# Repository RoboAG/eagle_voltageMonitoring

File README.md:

# eagle_voltageMonitoring
Simple voltage monitoring circuit

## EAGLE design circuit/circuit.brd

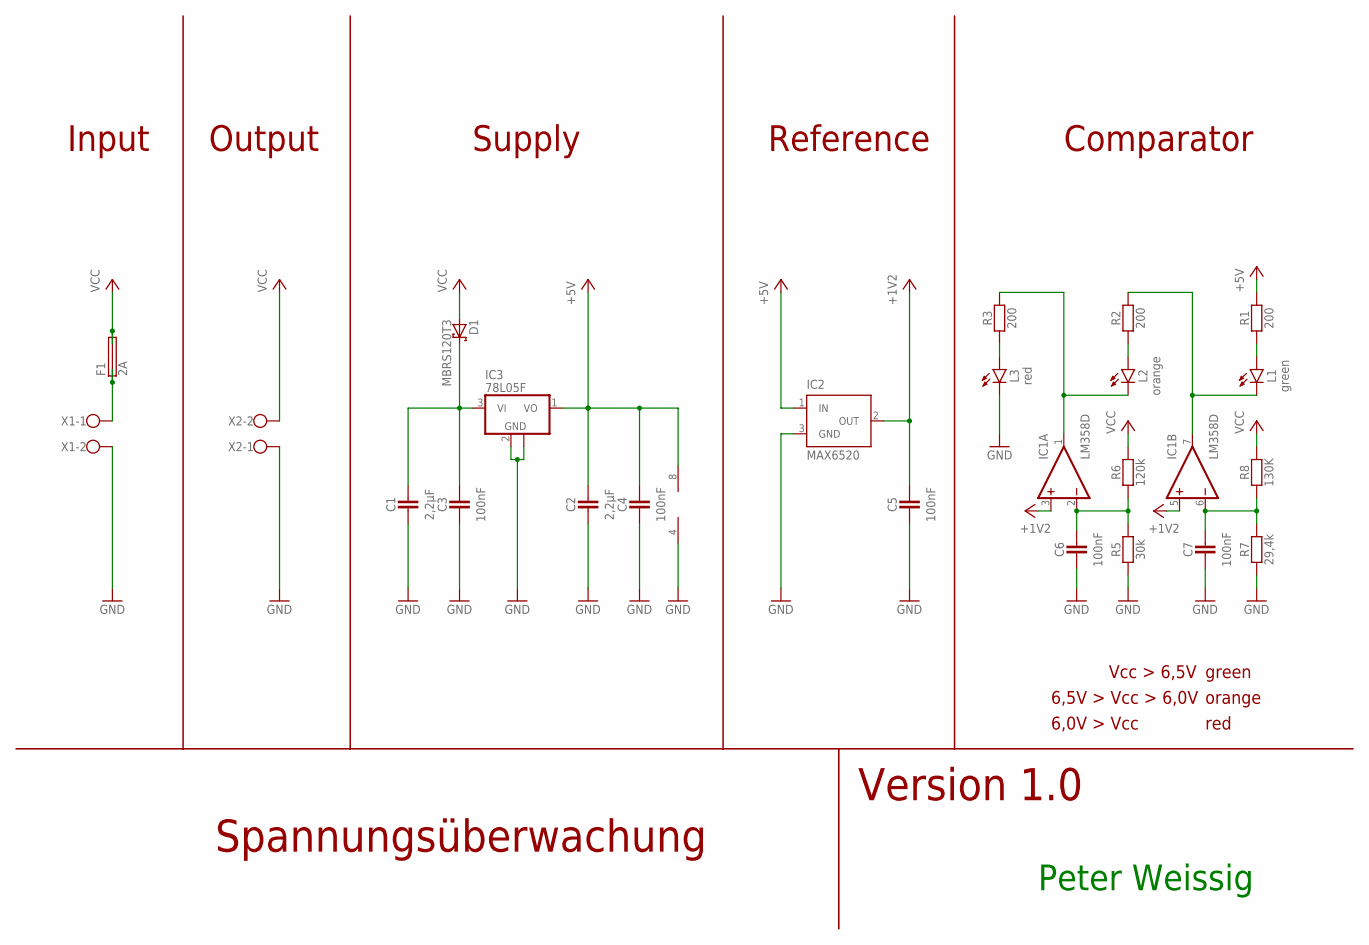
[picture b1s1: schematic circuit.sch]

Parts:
C1, C2: 2,2µF; SMD_1206
C3, C4, C5, C6, C7: 100nF; SMD_1206
D1: MBRS120T3; SMB
F1: 2A; SHK20L
IC1: LM358D; SO08
IC2: MAX6520; SOT23
IC3: 78L05F; SOT89
L1: green; LED_3MM
L2: orange; LED_3MM
L3: red; LED_3MM
R1, R2, R3: 200; SMD_1206
R5: 30k; SMD_1206
R6: 120k; SMD_1206
R7: 29,4k; SMD_1206
R8: 130K; SMD_1206
X1, X2: W237-102

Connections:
+3V3: C5.1, IC1.3 (+IN), IC1.5 (+IN), IC2.2 (OUT)
+5V: C2.1, C4.1, IC1.8 (V+), IC2.1 (IN), IC3.1 (VO), R1.1
GND: C1.2, C2.2, C3.2, C4.2, C5.2, C6.2, C7.2, IC1.4 (V-), IC2.3 (GND), IC3.2 (GND), IC3.2@1 (GND), L3.K (C), R5.1, R7.1, X1.2, X2.1
unnamed: C6.1, IC1.2 (-IN), R5.2, R6.1
unnamed: F1.1A, F1.1B, X1.1
unnamed: C7.1, IC1.6 (-IN), R7.2, R8.1
unnamed: C1.1, C3.1, D1.C, IC3.3 (VI)
unnamed: L1.A, R1.2
unnamed: IC1.7 (OUT), L1.K (C), R2.1
unnamed: L3.A, R3.2
unnamed: IC1.1 (OUT), L2.K (C), R3.1
unnamed: L2.A, R2.2
VCC: D1.A, F1.2A, F1.2B, R6.2, R8.2, X2.2

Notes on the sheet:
Input
Spannungsüberwachung
Peter Weissig
Version 1.0
Supply
Comparator
Output
Reference
Vcc > 6,5V
6,5V > Vcc > 6,0V
6,0V > Vcc
green
orange
red

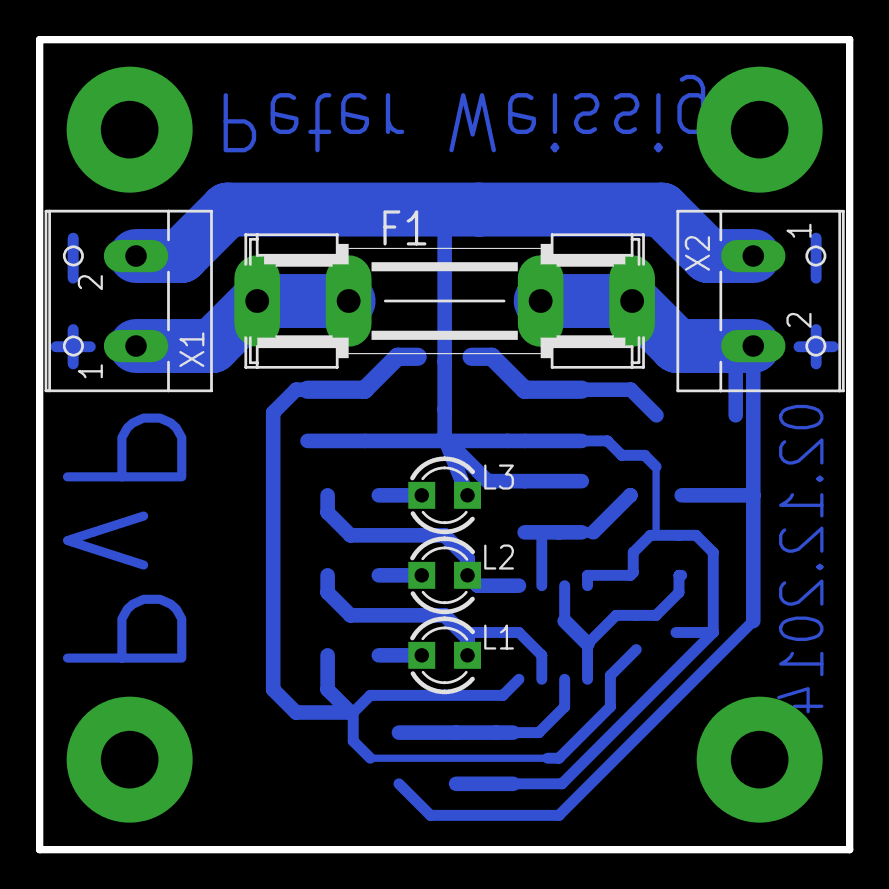
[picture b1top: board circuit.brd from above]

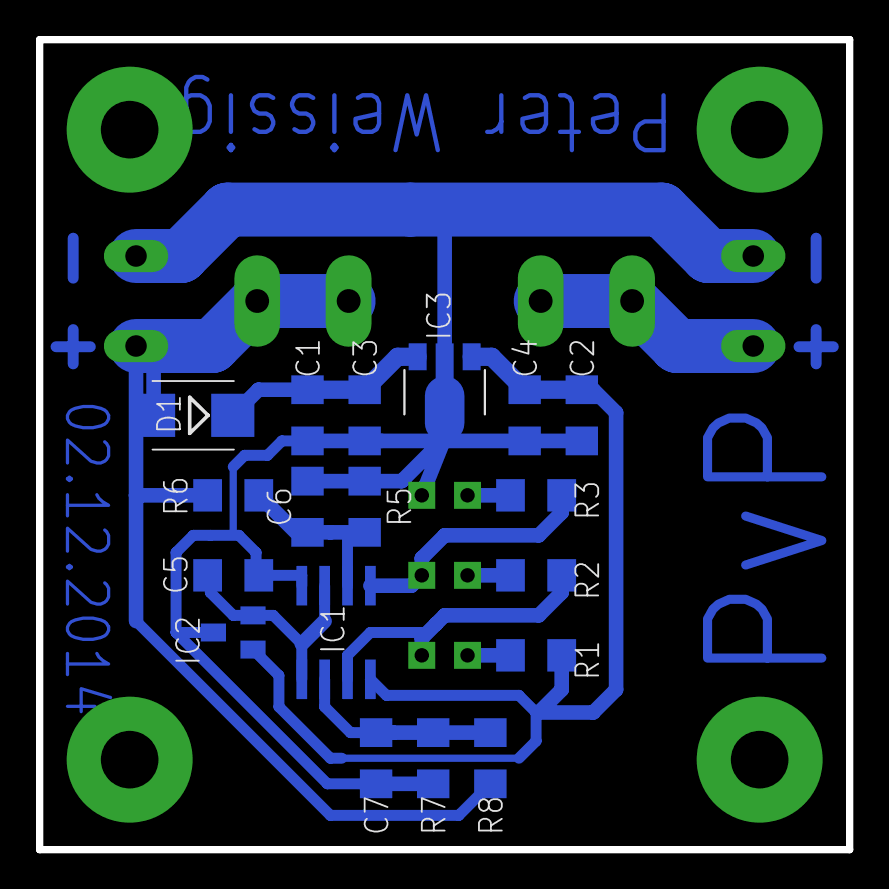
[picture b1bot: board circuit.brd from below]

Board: 2 copper layers, 45.0 x 45.0 mm, 24 parts (18 on the bottom side), 13 nets.

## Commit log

2017-11-26 updated year within license (2014-2017)
